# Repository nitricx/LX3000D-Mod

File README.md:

# LX3000D-Mod
Modification to a Phillips 5.1 Home-Theater to be able to have a 5.1 input from an analog source

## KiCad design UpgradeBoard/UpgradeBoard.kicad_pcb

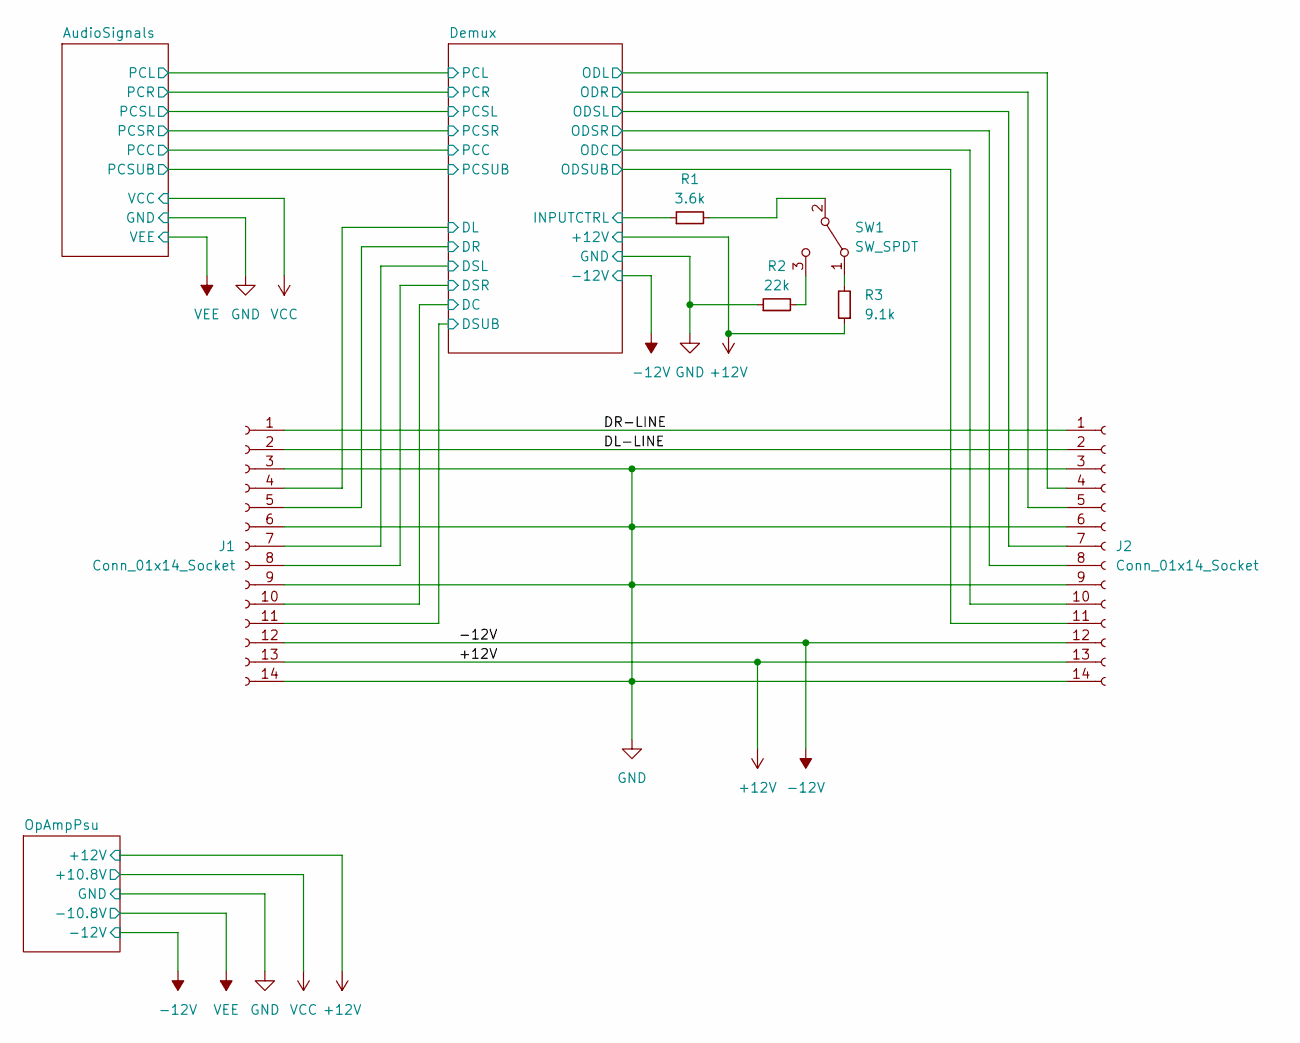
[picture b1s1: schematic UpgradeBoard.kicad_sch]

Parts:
J1, J2: Conn_01x14_Socket; Hirose_FH12-14S-0.5SH_1x14-1MP_P0.50mm_Horizontal
R1: 3.6k; R_0603_1608Metric
R2: 22k; R_0603_1608Metric
R3: 9.1k; R_0603_1608Metric
SW1: SW_SPDT; SW_CuK_OS102011MA1QN1_SPDT_Angled

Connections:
+12V: J1.13, J2.13, R3.1; also elsewhere on the board
-12V: J1.12, J2.12; also elsewhere on the board
/DL-LINE: J1.2, J2.2
/DR-LINE: J1.1, J2.1
/Demux/DC: J1.10; also elsewhere on the board
/Demux/DL: J1.4; also elsewhere on the board
/Demux/DR: J1.5; also elsewhere on the board
/Demux/DSL: J1.7; also elsewhere on the board
/Demux/DSR: J1.8; also elsewhere on the board
/Demux/DSUB: J1.11; also elsewhere on the board
/Demux/INPUTCTRL: R1.1; also elsewhere on the board
/Demux/ODC: J2.10; also elsewhere on the board
/Demux/ODL: J2.4; also elsewhere on the board
/Demux/ODR: J2.5; also elsewhere on the board
/Demux/ODSL: J2.7; also elsewhere on the board
/Demux/ODSR: J2.8; also elsewhere on the board
/Demux/ODSUB: J2.11; also elsewhere on the board
unnamed: R3.2, SW1.1 (A)
unnamed: R1.2, SW1.2 (B)
unnamed: R2.2, SW1.3 (C)

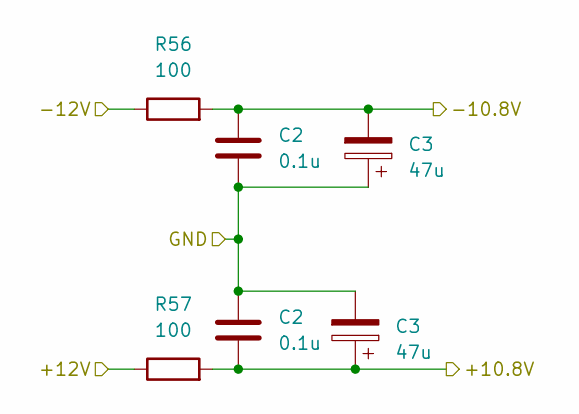
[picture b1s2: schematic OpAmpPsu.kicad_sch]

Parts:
C2: 0.1u; C_0805_2012Metric; JLC C2929181
C3: 47u; C_2220_5650Metric; JLC C600189
R56, R57: 100; R_0805_2012Metric; JLC C17408

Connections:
+12V: R57.1; also elsewhere on the board
-12V: R56.1; also elsewhere on the board

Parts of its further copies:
C41, C42: 0.1u; C_0805_2012Metric; JLC C2929181
C43, C44: 47u; C_2220_5650Metric; JLC C600189

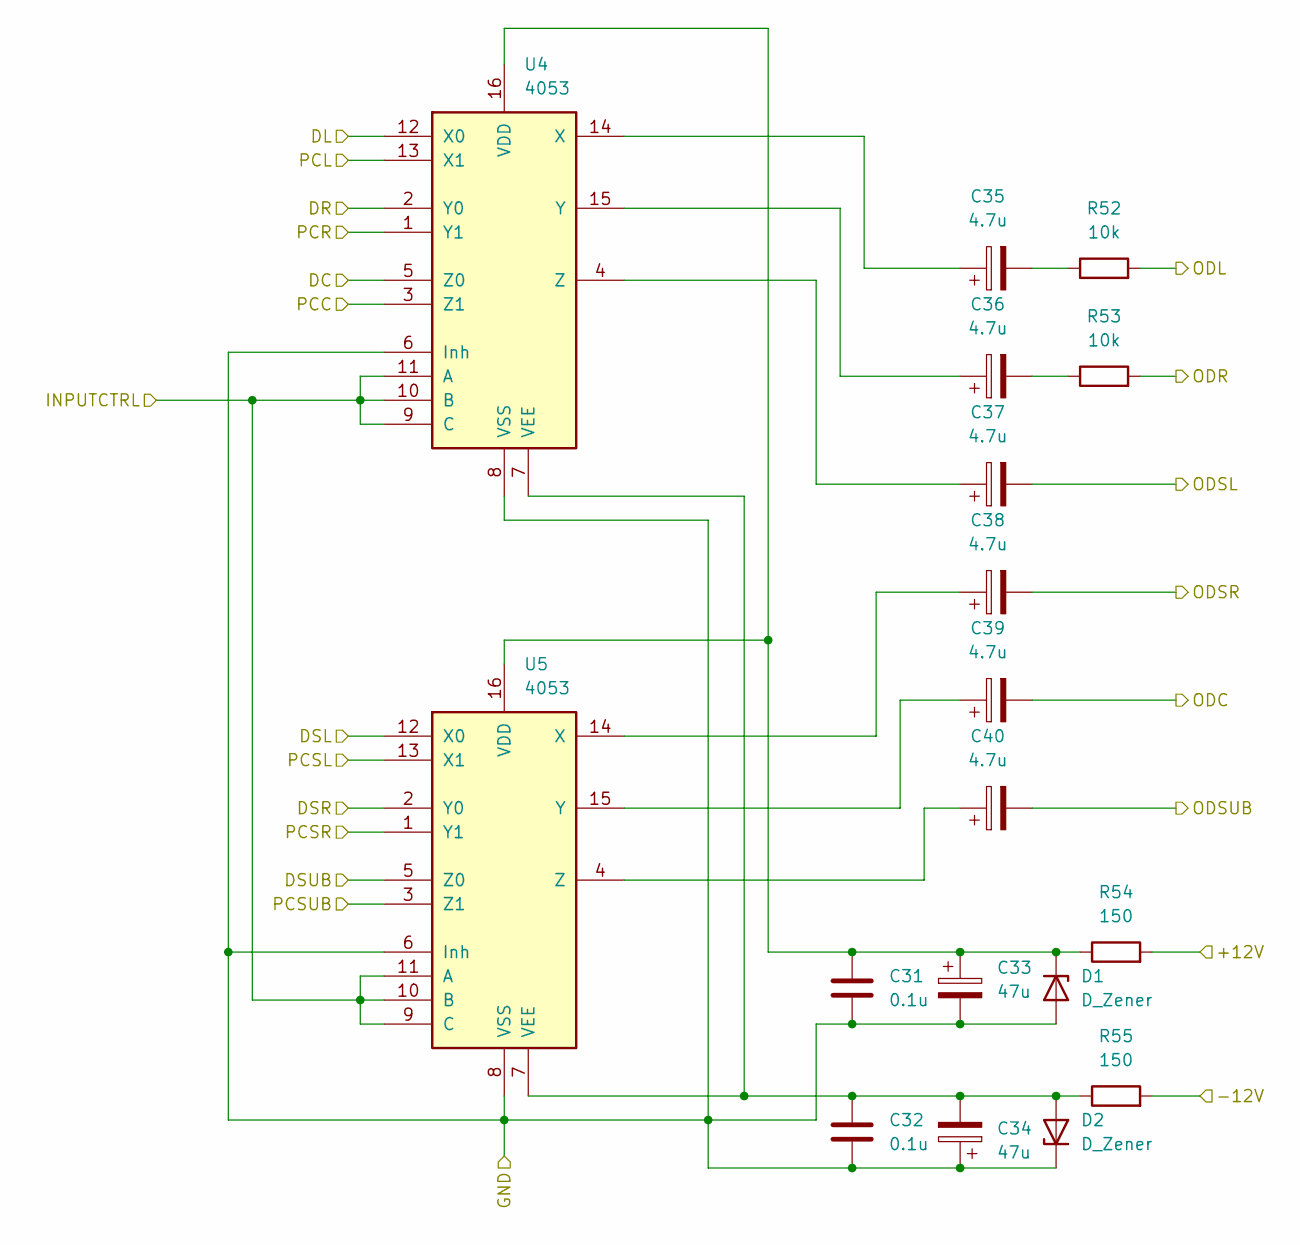
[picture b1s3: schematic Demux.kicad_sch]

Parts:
C31, C32: 0.1u; C_0805_2012Metric; JLC C2929181
C33, C34: 47u; C_2220_5650Metric; JLC C600189
C35, C36, C37, C38, C39, C40: 4.7u; C_1206_3216Metric; JLC C915818
D1, D2: D_Zener; D_0603_1608Metric
R52, R53: 10k; R_0603_1608Metric; JLC C25804
R54, R55: 150; R_0805_2012Metric; JLC C2988914
U4, U5: 4053; TSSOP-16_4.4x5mm_P0.65mm; JLC C131090

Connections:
+12V: R54.2; also elsewhere on the board
-12V: R55.2; also elsewhere on the board
/AudioSignals/PCC: U4.3 (Z1); also elsewhere on the board
/AudioSignals/PCL: U4.13 (X1); also elsewhere on the board
/AudioSignals/PCR: U4.1 (Y1); also elsewhere on the board
/AudioSignals/PCSL: U5.13 (X1); also elsewhere on the board
/AudioSignals/PCSR: U5.1 (Y1); also elsewhere on the board
/AudioSignals/PCSUB: U5.3 (Z1); also elsewhere on the board
/Demux/DC: U4.5 (Z0); also elsewhere on the board
/Demux/DL: U4.12 (X0); also elsewhere on the board
/Demux/DR: U4.2 (Y0); also elsewhere on the board
/Demux/DSL: U5.12 (X0); also elsewhere on the board
/Demux/DSR: U5.2 (Y0); also elsewhere on the board
/Demux/DSUB: U5.5 (Z0); also elsewhere on the board
/Demux/INPUTCTRL: U4.9 (C), U4.10 (B), U4.11 (A), U5.9 (C), U5.10 (B), U5.11 (A); also elsewhere on the board
/Demux/ODC: C39.2; also elsewhere on the board
/Demux/ODL: R52.2; also elsewhere on the board
/Demux/ODR: R53.2; also elsewhere on the board
/Demux/ODSL: C37.2; also elsewhere on the board
/Demux/ODSR: C38.2; also elsewhere on the board
/Demux/ODSUB: C40.2; also elsewhere on the board
unnamed: C35.2, R52.1
unnamed: C36.2, R53.1
unnamed: C31.1, C33.1, D1.1 (K), R54.1, U4.16 (VDD), U5.16 (VDD)
unnamed: C32.1, C34.2, D2.2 (A), R55.1, U4.7 (VEE), U5.7 (VEE)
unnamed: C35.1, U4.14 (X)
unnamed: C36.1, U4.15 (Y)
unnamed: C37.1, U4.4 (Z)
unnamed: C38.1, U5.14 (X)
unnamed: C39.1, U5.15 (Y)
unnamed: C40.1, U5.4 (Z)

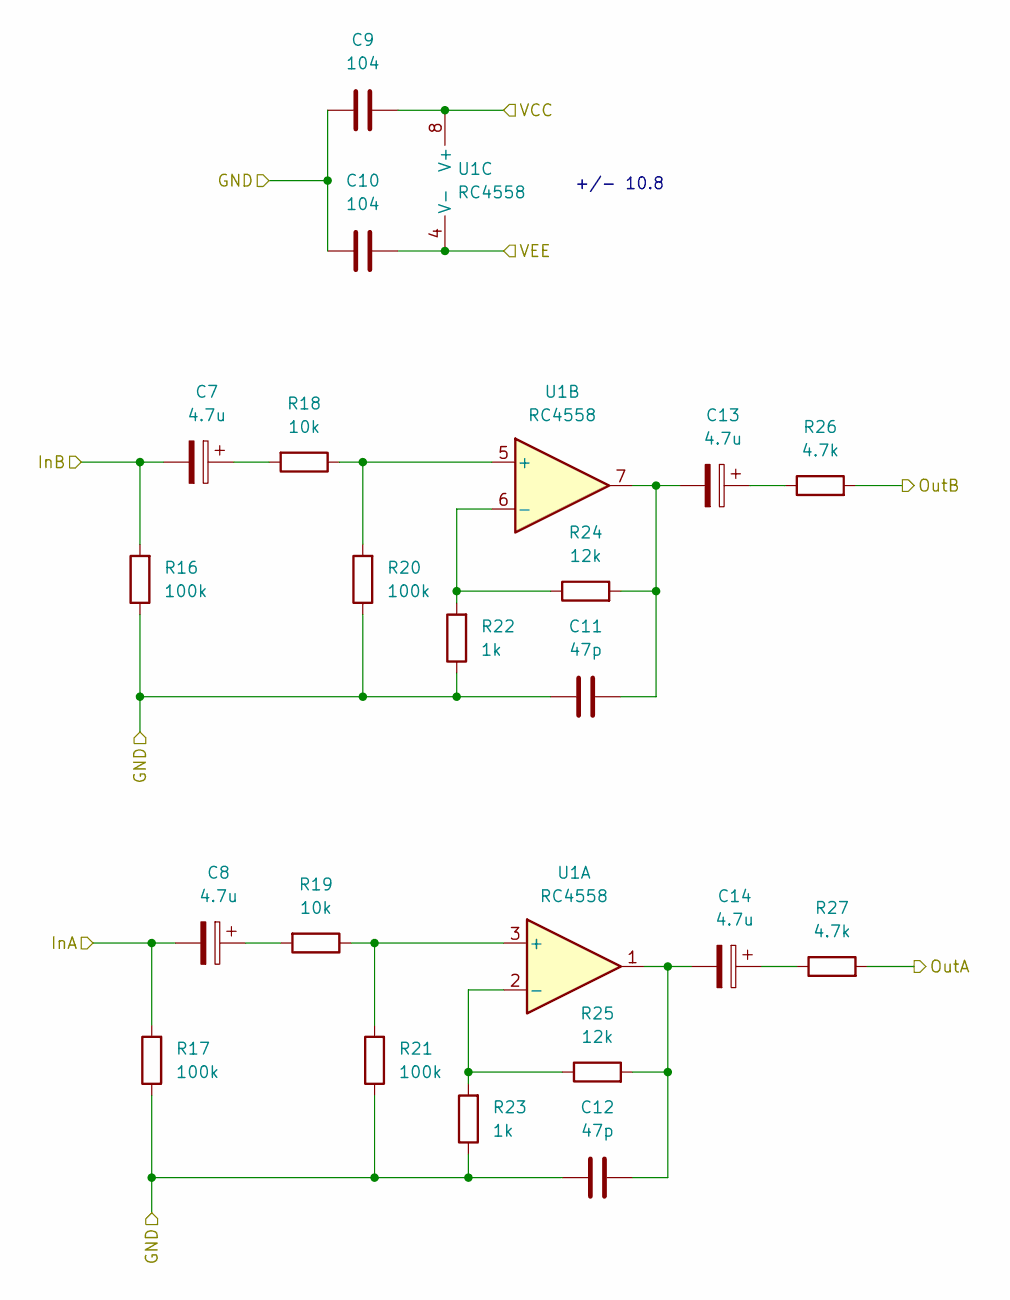
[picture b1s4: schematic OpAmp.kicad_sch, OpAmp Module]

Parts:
C7, C8, C13, C14: 4.7u; C_1206_3216Metric; JLC C915818
C9, C10: 104; C_0805_2012Metric; JLC C2929181
C11, C12: 47p; C_0805_2012Metric; JLC C376889
R16, R17, R20, R21: 100k; R_1206_3216Metric; JLC C965069
R18, R19: 10k; R_1206_3216Metric
R22, R23: 1k; R_0603_1608Metric; JLC C21190
R24, R25: 12k; R_1206_3216Metric; JLC C2771295
R26, R27: 4.7k; R_0805_2012Metric; JLC C380775
U1: RC4558; SOIC-8_3.9x4.9mm_P1.27mm; JLC C406864

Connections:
/AudioSignals/FrontAudioConnectors/R: C8.2, R17.2; also elsewhere on the board
/AudioSignals/FrontAudioConnectors/T: C7.2, R16.2; also elsewhere on the board
/AudioSignals/PCL: R27.2; also elsewhere on the board
/AudioSignals/PCR: R26.2; also elsewhere on the board
unnamed: C7.1, R18.2
unnamed: C8.1, R19.2
unnamed: C11.2, C13.2, R24.2, U1.7
unnamed: C12.2, C14.2, R25.2, U1.1
unnamed: C13.1, R26.1
unnamed: C14.1, R27.1
unnamed: R19.1, R21.2, U1.3 (+)
unnamed: R23.2, R25.1, U1.2 (-)
unnamed: R18.1, R20.2, U1.5 (+)
unnamed: R22.2, R24.1, U1.6 (-)

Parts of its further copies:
C15, C16, C21, C22, C23, C24, C29, C30: 4.7u; C_1206_3216Metric; JLC C915818
C17, C18, C25, C26: 104; C_0805_2012Metric; JLC C2929181
C19, C20, C27, C28: 47p; C_0805_2012Metric; JLC C376889
R28, R29, R32, R33, R40, R41, R44, R45: 100k; R_1206_3216Metric; JLC C965069
R30, R31, R42, R43: 10k; R_1206_3216Metric
R34, R35, R46, R47: 1k; R_0603_1608Metric; JLC C21190
R36, R37, R48, R49: 12k; R_1206_3216Metric; JLC C2771295
R38, R39, R50, R51: 4.7k; R_0805_2012Metric; JLC C380775
U2, U3: RC4558; SOIC-8_3.9x4.9mm_P1.27mm; JLC C406864

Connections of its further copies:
/AudioSignals/CenterSubAudioConnectors/R: C24.2, R41.2; also elsewhere on the board
/AudioSignals/CenterSubAudioConnectors/T: C23.2, R40.2; also elsewhere on the board
/AudioSignals/PCC: R51.2; also elsewhere on the board
/AudioSignals/PCSL: R39.2; also elsewhere on the board
/AudioSignals/PCSR: R38.2; also elsewhere on the board
/AudioSignals/PCSUB: R50.2; also elsewhere on the board
/AudioSignals/SorroundAudioConnectors/R: C16.2, R29.2; also elsewhere on the board
/AudioSignals/SorroundAudioConnectors/T: C15.2, R28.2; also elsewhere on the board
unnamed: C15.1, R30.2
unnamed: C16.1, R31.2
unnamed: C19.2, C21.2, R36.2, U2.7
unnamed: C20.2, C22.2, R37.2, U2.1
unnamed: C21.1, R38.1
unnamed: C22.1, R39.1
unnamed: C23.1, R42.2
unnamed: C24.1, R43.2
unnamed: C27.2, C29.2, R48.2, U3.7
unnamed: C28.2, C30.2, R49.2, U3.1
unnamed: C29.1, R50.1
unnamed: C30.1, R51.1
unnamed: R31.1, R33.2, U2.3 (+)
unnamed: R35.2, R37.1, U2.2 (-)
unnamed: R30.1, R32.2, U2.5 (+)
unnamed: R34.2, R36.1, U2.6 (-)
unnamed: R43.1, R45.2, U3.3 (+)
unnamed: R47.2, R49.1, U3.2 (-)
unnamed: R42.1, R44.2, U3.5 (+)
unnamed: R46.2, R48.1, U3.6 (-)

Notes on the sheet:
+/- 10.8

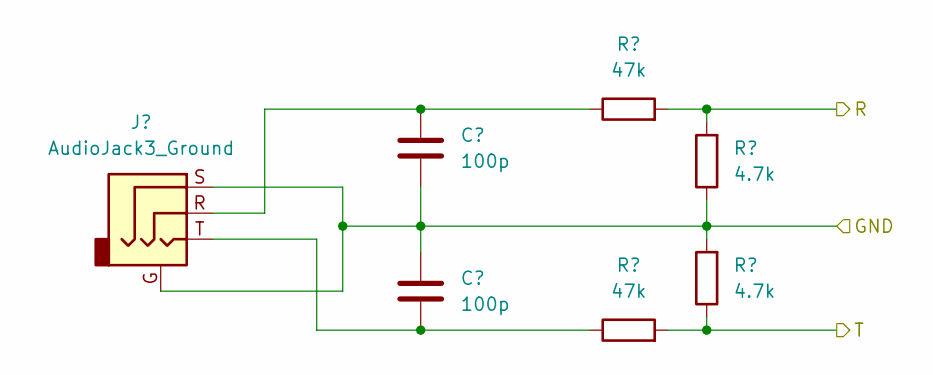
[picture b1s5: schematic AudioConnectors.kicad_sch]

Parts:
C3, C4: 100p; C_0603_1608Metric; JLC C576781
J4: AudioJack3_Ground; Jack_3.5mm_CUI_SJ-3524-SMT_Horizontal
R8, R9: 47k; R_0805_2012Metric; JLC C2759457
R10, R11: 4.7k; R_0805_2012Metric; JLC C380775

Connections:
/AudioSignals/FrontAudioConnectors/R: R8.2, R10.2; also elsewhere on the board
/AudioSignals/FrontAudioConnectors/T: R9.2, R11.1; also elsewhere on the board
unnamed: C4.2, J4.T, R9.1

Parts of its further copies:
C1, C5, C6: 100p; C_0603_1608Metric; JLC C576781
J3, J5: AudioJack3_Ground; Jack_3.5mm_CUI_SJ-3524-SMT_Horizontal
R4, R5, R12, R13: 47k; R_0805_2012Metric; JLC C2759457
R6, R7, R14, R15: 4.7k; R_0805_2012Metric; JLC C380775

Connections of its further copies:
/AudioSignals/CenterSubAudioConnectors/R: R4.2, R6.2; also elsewhere on the board
/AudioSignals/CenterSubAudioConnectors/T: R5.2, R7.1; also elsewhere on the board
/AudioSignals/SorroundAudioConnectors/R: R12.2, R14.2; also elsewhere on the board
/AudioSignals/SorroundAudioConnectors/T: R13.2, R15.1; also elsewhere on the board
unnamed: C1.1, J3.R, R4.1
unnamed: C5.1, J5.R, R12.1
unnamed: C6.2, J5.T, R13.1

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
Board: 2 copper layers, 114 parts (0 on the bottom side), 81 nets, no tracks yet.

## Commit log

2023-04-10 init
2023-04-11 opamp terminado
2023-04-11 audio input terminado
2023-04-13 Demux module completed
2023-04-13 10.8 PSU done
2023-10-31 updated repo and bkp state
2023-11-23 KicadUpgrade
    Project reset
2023-11-23 relinked files
2023-11-24 friday update
    new hierarchical sheets, cabling, switching for main demux
2023-11-25 psucorrection
2023-11-25 updated components
    added footprint and jlcpcb component number
2023-11-27 more components definition
